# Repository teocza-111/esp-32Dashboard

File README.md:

# Overview
An esp-32 based dashboard with a 4.2" e-ink display from waveshare.
## Why?
Its main purpouse is just sitting on a desk and looking nice, nothing much besides that.
## Features
- Displaying current spotify playing song
- Time and date
- Weather
- [WIP]
# Part List
- [Seeed Studio Xiao ESP32-S3 Plus](https://kamami.pl/xiao/1195704-xiao-esp32s3-plus-plytka-rozwojowa-z-mikrokontrolerem-esp32s3-5906623496303.html)
- [Waveshare 4.2" e-ink display](https://botland.com.pl/wyswietlacze-e-paper/9655-e-paper-e-ink-42-400x300px-modul-z-wyswietlaczem-spi-waveshare-13353-5904422338312.html)
- [4000mAh li-po](https://botland.com.pl/akumulatory-li-pol-1s-37v/15644-akumulator-li-pol-akyga-4000mah-1s-37v-zlacze-jst-bec-gniazdo-80x50x8mm-5904422343644.html)
- 2 * 100kOhm Resistors -- i already own them
- [JST-BEC female adapter](https://botland.com.pl/akcesoria-do-akumulatorow/2865-para-konektorow-jst-bec-do-akumulatorow-li-pol-5904422331221.html)
- Male pin headers 8x2.54mm -- They come with the display
# Media
## Schematics & PCB

## Renders [WIP]

## Bill of materials
|Name                           |Purpose                                   |Quantity|Total Cost (USD)|Link                                                |Distributor    |
|-------------------------------|------------------------------------------|--------|----------------|----------------------------------------------------|---------------|
|JST-PH 2.0 Female              |Connecting the battery to the mcu         |1       |0.84            |https://pl.aliexpress.com/item/4000199807342.htm    |AliExpress     |
|100kOhm Resistors              |Safely reading the volatage of the battery|2       |0.00            |                                                    |My resistor kit|
|4000mAh li-po battery          |The power source                          |1       |9.48            |https://pl.aliexpress.com/item/1005009889665207.html|AliExpress     |
|Seeed Studio Xiao ESP32-S3 Plus|MCU                                       |1       |12.46           |https://pl.aliexpress.com/item/1005010291070801.html|AliExpress     |
|Waveshare 4.2" e-ink display   |The display                               |1       |39.44           |https://pl.aliexpress.com/item/1005004260969887.html|AliExpress     |
|PCB                            |It's... Well a PCB                        |1       |10.00           |                                                    |JLCPCB         |

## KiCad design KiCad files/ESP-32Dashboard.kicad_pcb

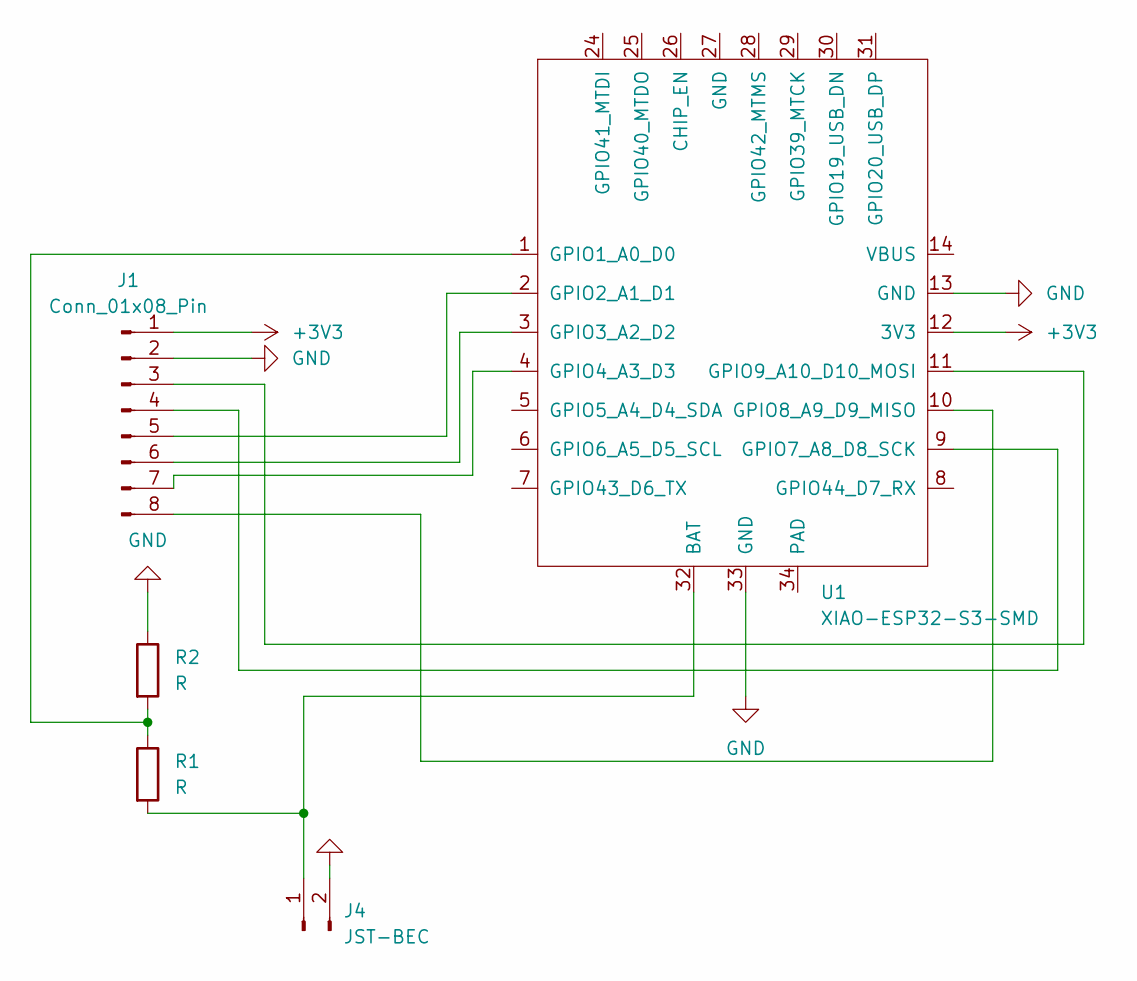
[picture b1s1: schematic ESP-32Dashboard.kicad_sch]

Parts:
J1: Conn_01x08_Pin; PinHeader_1x08_P2.54mm_Vertical
J4: JST-BEC; PinHeader_1x02_P2.54mm_Vertical
R1, R2: R; R_Axial_DIN0207_L6.3mm_D2.5mm_P10.16mm_Horizontal
U1: XIAO-ESP32-S3-SMD; XIAO-ESP32-S3-Plus-SMD

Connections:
+3V3: J1.1, U1.12 (3V3)
GND: J1.2, J4.2, R2.1, U1.13 (GND), U1.33 (GND)
unnamed: J1.3, U1.11 (GPIO9_A10_D10_MOSI)
unnamed: J1.4, U1.9 (GPIO7_A8_D8_SCK)
unnamed: J1.5, U1.2 (GPIO2_A1_D1)
unnamed: J1.6, U1.3 (GPIO3_A2_D2)
unnamed: J1.7, U1.4 (GPIO4_A3_D3)
unnamed: J1.8, U1.10 (GPIO8_A9_D9_MISO)
unnamed: J4.1, R1.2, U1.32 (BAT)
unnamed: R1.1, R2.2, U1.1 (GPIO1_A0_D0)

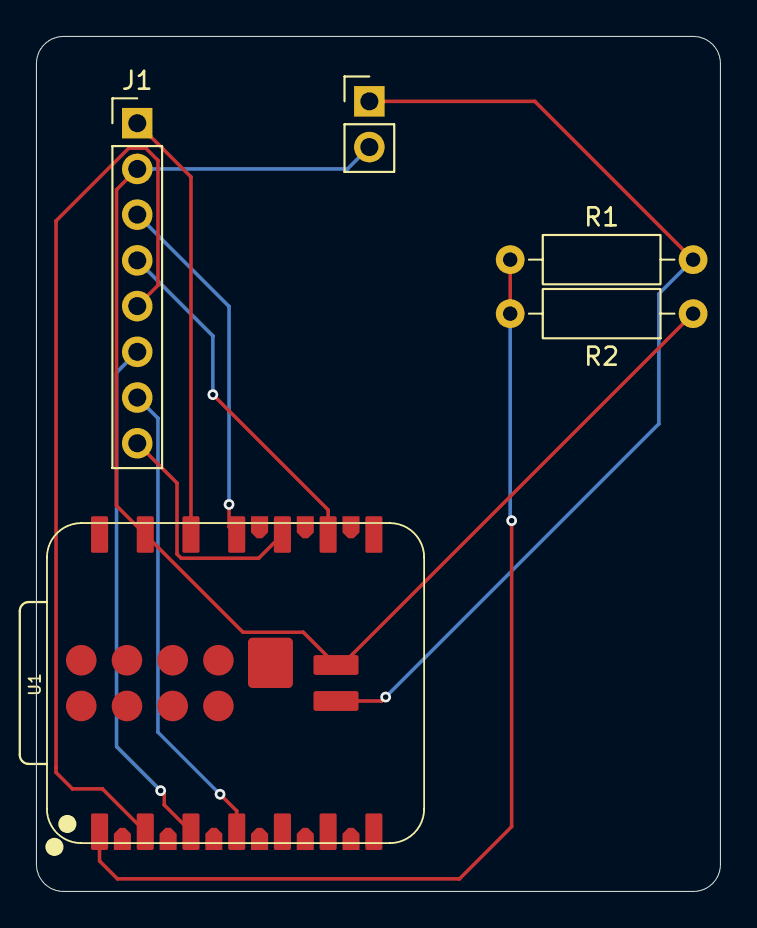
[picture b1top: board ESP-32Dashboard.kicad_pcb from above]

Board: 2 copper layers, 38.0 x 47.5 mm, 5 parts (0 on the bottom side), 10 nets.

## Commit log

2026-04-25 Added Kicad and media files
2026-04-25 Add initial README
2026-05-05 Revise README with purpose and updated parts
    Updated part list and added a section explaining the purpose of the dashboard.
2026-05-05 Small changes to the pcb + new renders
2026-05-05 Enhance README with part details and media section
    Updated part list with a link for the 4000mAh li-po battery and added media section with schematics, PCB, and renders.
2026-05-24 Revise part list in README with links and notes
    Updated part list with links and notes on ownership.
2026-05-30 Added a BoM
2026-05-30 Added a jorunal
2026-05-30 Add bill of materials to README
    Added a bill of materials section with details on components used in the project.
2026-05-30 Fix formatting in JOURNAL.md entry
2026-05-30 Update JOURNAL.md with project details
    Added metadata for the esp32-Dashboard project.
2026-05-30 Revise time entries and add CAD progress
    Updated time spent on various tasks and added new entry for CAD work.
2026-05-31 Revise JOURNAL.md with recent project updates
    Updated journal entries with new research, PCB details, and firmware progress. Added images and clarified time spent on tasks.
2026-06-05 fixed edge.cuts
2026-06-06 V1 case
2026-06-11 Created the stand
2026-06-11 Rename esp-32Dashboard-bom.csv to bom.csv
